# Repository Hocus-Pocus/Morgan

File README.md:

# Morgan
2001 Dodge Ram 2500, 4x4, Extended cab, Long box. Originally equiped with the 360CID V8 engine, automatic transmision and Dana 60 HD rear axle. Drive train changed to 1995 Dodge 488CID (8.0L) V 10 engine, NV4500 5 speed manual transmission, Dana 80 limited slip rear axle, custom built programmable EFI.

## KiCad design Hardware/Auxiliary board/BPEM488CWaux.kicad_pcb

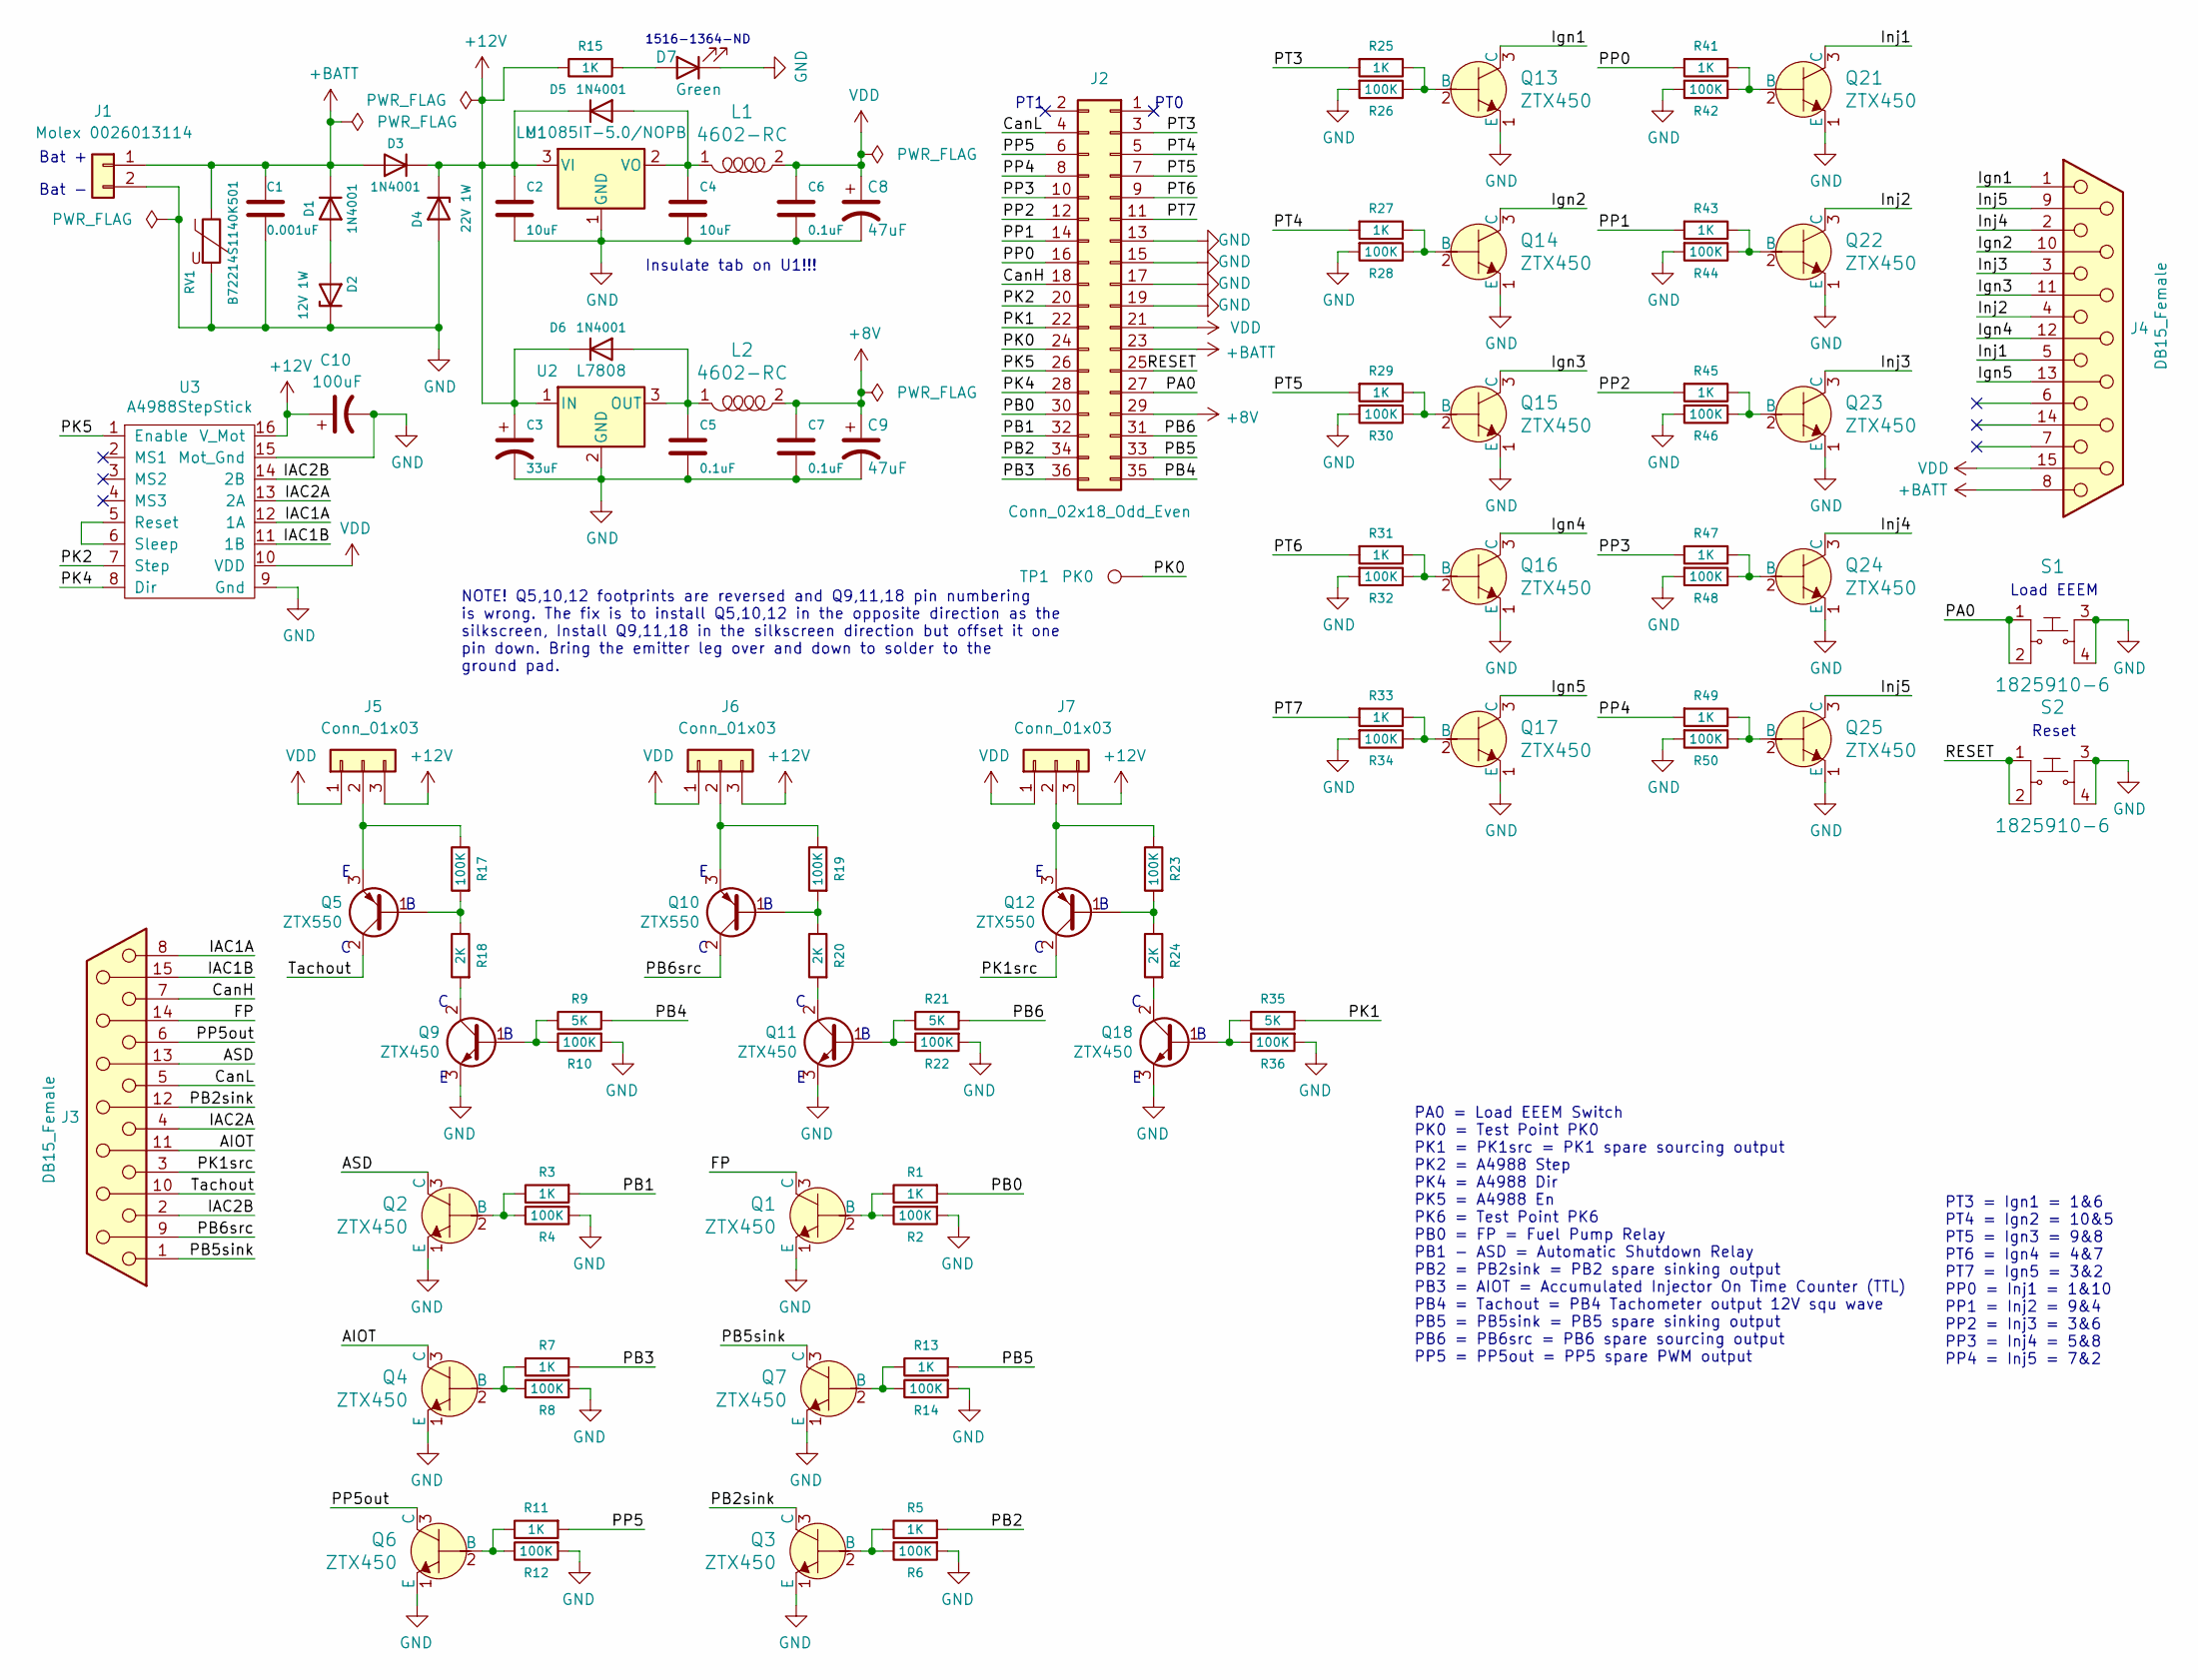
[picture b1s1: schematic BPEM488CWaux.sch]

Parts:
C1: 0.001uF; C_Disc_D3.8mm_W2.6mm_P2.50mm; Digikey 399-13913-2-ND
C2, C4: 10uF; C_Disc_D5.0mm_W2.5mm_P2.50mm; Digikey 399-13950-ND
C3: 33uF; CP_Radial_Tantal_D8.0mm_P5.00mm; Digikey 399-3591-ND
C5, C6, C7: 0.1uF; C_Disc_D5.0mm_W2.5mm_P2.50mm; Digikey 399-4264-ND
C8, C9: 47uF; CP_Radial_Tantal_D8.0mm_P5.00mm; Digikey 399-3596-ND
C10: 100uF; CP_Radial_Tantal_D8.0mm_P5.00mm; Digikey 399-3596-ND
D1, D3, D5, D6: 1N4001; D_DO-41_SOD81_P7.62mm_Horizontal; Digikey 1N4001DICT-ND
D2: 12V 1W; D_DO-41_SOD81_P7.62mm_Horizontal; Digikey 1727-3635-2-ND
D4: 22V 1W; D_DO-41_SOD81_P7.62mm_Horizontal; Digikey MAZ222000GTR-ND
D7: Green; LED_D5.0mm; Digikey 1516-1364-ND
J1: Molex 0026013114; Molex_Mini-Fit_Jr_5569-02A2_2x01_P4.20mm_Horizontal; Digikey WM14505-ND
J2: Conn_02x18_Odd_Even; PinSocket_2x18_P2.54mm_Vertical
J3, J4: DB15_Female; DSUB-15_Female_Horizontal_P2.77x2.84mm_EdgePinOffset7.70mm_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; Digikey A32123-ND
J5, J6, J7: Conn_01x03; PinHeader_1x03_P2.54mm_Vertical
L1, L2: 4602-RC; L_Axial_L16.0mm_D6.3mm_P25.40mm_Horizontal_Fastron_VHBCC; Digikey 4602-RC-ND
Q1, Q2, Q3, Q4, Q6, Q7, Q13, Q14, Q15, Q16, Q17, Q21, Q22, Q23, Q24, Q25: ZTX450; MPN ZTX450; Digi-Key_PN ZTX450-ND
Q5, Q10, Q12: ZTX550
Q9, Q11, Q18: ZTX450
R1, R3, R5, R7, R11, R13, R15, R25, R27, R29, R31, R33, R41, R43, R45, R47, R49: 1K; R_Axial_DIN0207_L6.3mm_D2.5mm_P10.16mm_Horizontal; Digikey 1.00KXBK-ND
R2, R4, R6, R8, R10, R12, R14, R22, R26, R28, R30, R32, R34, R36, R42, R44, R46, R48, R50: 100K; R_Axial_DIN0207_L6.3mm_D2.5mm_P10.16mm_Horizontal; Digikey 100KXBK-ND
R9, R21, R35: 5K; R_Axial_DIN0207_L6.3mm_D2.5mm_P10.16mm_Horizontal; Digikey 1.00KXBK-ND
R17, R19, R23: 100K; R_Axial_DIN0207_L6.3mm_D2.5mm_P10.16mm_Horizontal; Digikey 1.00KXBK-ND
R18, R20, R24: 2K; R_Axial_DIN0207_L6.3mm_D2.5mm_P10.16mm_Horizontal; Digikey 1.00KXBK-ND
RV1: B72214S1140K501; RV_Disc_D15.5mm_W3.9mm_P7.5mm; Digikey 495-2057-ND
S1, S2: 1825910-6; Switch_Tactile_THT_6x6mm; MPN 1825910-6; Digi-Key_PN 450-1650-ND
TP1: PK0; PinHeader_1x01_P2.54mm_Vertical
U1: LM1085IT-5.0/NOPB; LM1085
U2: L7808
U3: A4988StepStick

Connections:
+8V: C7.1, C9.1, J2.29, L2.2
+12V: C2.1, C3.1, C10.1, D3.1 (K), D4.1 (K), D5.1 (K), D6.1 (K), J5.3, J6.3, J7.3, R15.1, U1.3 (VI), U2.1 (IN), U3.16 (V_Mot)
+BATT: C1.1, D1.1 (K), D3.2 (A), J1.1, J2.23, J4.8, RV1.1
/AIOT: J3.11 (P111), Q4.3 (C)
/ASD: J3.13, Q2.3 (C)
/CanH: J2.18, J3.7
/CanL: J2.4, J3.5
/FP: J3.14, Q1.3 (C)
/IAC1A: J3.8, U3.12 (1A)
/IAC1B: J3.15, U3.11 (1B)
/IAC2A: J3.4, U3.13 (2A)
/IAC2B: J3.2, U3.14 (2B)
/Ign1: J4.1, Q13.3 (C)
/Ign2: J4.10, Q14.3 (C)
/Ign3: J4.11 (P111), Q15.3 (C)
/Ign4: J4.12, Q16.3 (C)
/Ign5: J4.13, Q17.3 (C)
/Inj1: J4.5, Q21.3 (C)
/Inj2: J4.4, Q22.3 (C)
/Inj3: J4.3, Q23.3 (C)
/Inj4: J4.2, Q24.3 (C)
/Inj5: J4.9, Q25.3 (C)
/PA0: J2.27, S1.1, S1.2
/PB0: J2.30, R1.2
/PB1: J2.32, R3.2
/PB2: J2.34, R5.2
/PB2sink: J3.12, Q3.3 (C)
/PB3: J2.36, R7.2
/PB4: J2.35, R9.2
/PB5: J2.33, R13.2
/PB5sink: J3.1, Q7.3 (C)
/PB6: J2.31, R21.2
/PB6src: J3.9, Q10.2 (C)
/PK0: J2.24, TP1.1
/PK1: J2.22, R35.2
/PK1src: J3.3, Q12.2 (C)
/PK2: J2.20, U3.7 (Step)
/PK4: J2.28, U3.8 (Dir)
/PK5: J2.26, U3.1 (Enable)
/PP0: J2.16, R41.2
/PP1: J2.14, R43.2
/PP2: J2.12, R45.2
/PP3: J2.10, R47.2
/PP4: J2.8, R49.2
/PP5: J2.6, R11.2
/PP5out: J3.6, Q6.3 (C)
/PT3: J2.3, R25.2
/PT4: J2.5, R27.2
/PT5: J2.7, R29.2
/PT6: J2.9, R31.2
/PT7: J2.11, R33.2
/RESET: J2.25, S2.1, S2.2
/Tachout: J3.10, Q5.2 (C)
GND: C1.2, C2.2, C3.2, C4.2, C5.2, C6.2, C7.2, C8.2, C9.2, C10.2, D2.1 (K), D4.2 (A), D7.1 (K), J1.2, J2.13, J2.15, J2.17, J2.19, Q1.1 (E), Q2.1 (E), Q3.1 (E), Q4.1 (E), Q6.1 (E), Q7.1 (E), Q9.3 (E), Q11.3 (E), Q13.1 (E), Q14.1 (E), Q15.1 (E), Q16.1 (E), Q17.1 (E), Q18.3 (E), Q21.1 (E), Q22.1 (E), Q23.1 (E), Q24.1 (E), Q25.1 (E), R2.2, R4.2, R6.2, R8.2, R10.2, R12.2, R14.2, R22.2, R26.2, R28.2, R30.2, R32.2, R34.2, R36.2, R42.2, R44.2, R46.2, R48.2, R50.2, RV1.2, S1.3, S1.4, S2.3, S2.4, U1.1 (GND), U2.2 (GND), U3.9 (Gnd), U3.15 (Mot_Gnd)
unnamed: C4.1, D5.2 (A), L1.1, U1.2 (VO)
unnamed: C5.1, D6.2 (A), L2.1, U2.3 (OUT)
unnamed: D1.2 (A), D2.2 (A)
unnamed: D7.2 (A), R15.2
unnamed: J5.2, Q5.3 (E), R17.1
unnamed: J6.2, Q10.3 (E), R19.1
unnamed: J7.2, Q12.3 (E), R23.1
unnamed: Q1.2 (B), R1.1, R2.1
unnamed: Q2.2 (B), R3.1, R4.1
unnamed: Q3.2 (B), R5.1, R6.1
unnamed: Q4.2 (B), R7.1, R8.1
unnamed: Q5.1 (B), R17.2, R18.1
unnamed: Q6.2 (B), R11.1, R12.1
unnamed: Q7.2 (B), R13.1, R14.1
unnamed: Q9.1 (B), R9.1, R10.1
unnamed: Q9.2 (C), R18.2
unnamed: Q10.1 (B), R19.2, R20.1
unnamed: Q11.1 (B), R21.1, R22.1
unnamed: Q11.2 (C), R20.2
unnamed: Q12.1 (B), R23.2, R24.1
unnamed: Q13.2 (B), R25.1, R26.1
unnamed: Q14.2 (B), R27.1, R28.1
unnamed: Q15.2 (B), R29.1, R30.1
unnamed: Q16.2 (B), R31.1, R32.1
unnamed: Q17.2 (B), R33.1, R34.1
unnamed: Q18.1 (B), R35.1, R36.1
unnamed: Q18.2 (C), R24.2
unnamed: Q21.2 (B), R41.1, R42.1
unnamed: Q22.2 (B), R43.1, R44.1
unnamed: Q23.2 (B), R45.1, R46.1
unnamed: Q24.2 (B), R47.1, R48.1
unnamed: Q25.2 (B), R49.1, R50.1
unnamed: U3.5 (Reset), U3.6 (Sleep)
VDD: C6.1, C8.1, J2.21, J4.15, J5.1, J6.1, J7.1, L1.2, U3.10 (VDD)

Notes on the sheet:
Load EEEM
Reset
Bat -
Bat +
PA0 = Load EEEM Switch PK0 = Test Point PK0 PK1 = PK1src = PK1 spare sourcing output PK2 = A4988 Step PK4 = A4988 Dir PK5 = A4988 En PK6 = Test Point PK6 PB0 = FP = Fuel Pump Relay PB1 - ASD = Automatic Shutdown Relay PB2 = PB2sink = PB2 spare sinking output PB3 = AIOT = Accumulated Injector On Tim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
PT3 = Ign1 = 1&6 PT4 = Ign2 = 10&5 PT5 = Ign3 = 9&8 PT6 = Ign4 = 4&7 PT7 = Ign5 = 3&2 PP0 = Inj1 = 1&10 PP1 = Inj2 = 9&4 PP2 = Inj3 = 3&6 PP3 = Inj4 = 5&8 PP4 = Inj5 = 7&2
Insulate tab on U1!!!
PT0
PT1
1516-1364-ND
NOTE! Q5,10,12 footprints are reversed and Q9,11,18 pin numbering is wrong. The fix is to install Q5,10,12 in the opposite direction as the silkscreen, Install Q9,11,18 in the silkscreen direction but offset it one pin down. Bring the emitter leg over and down to solder to the ground pad.

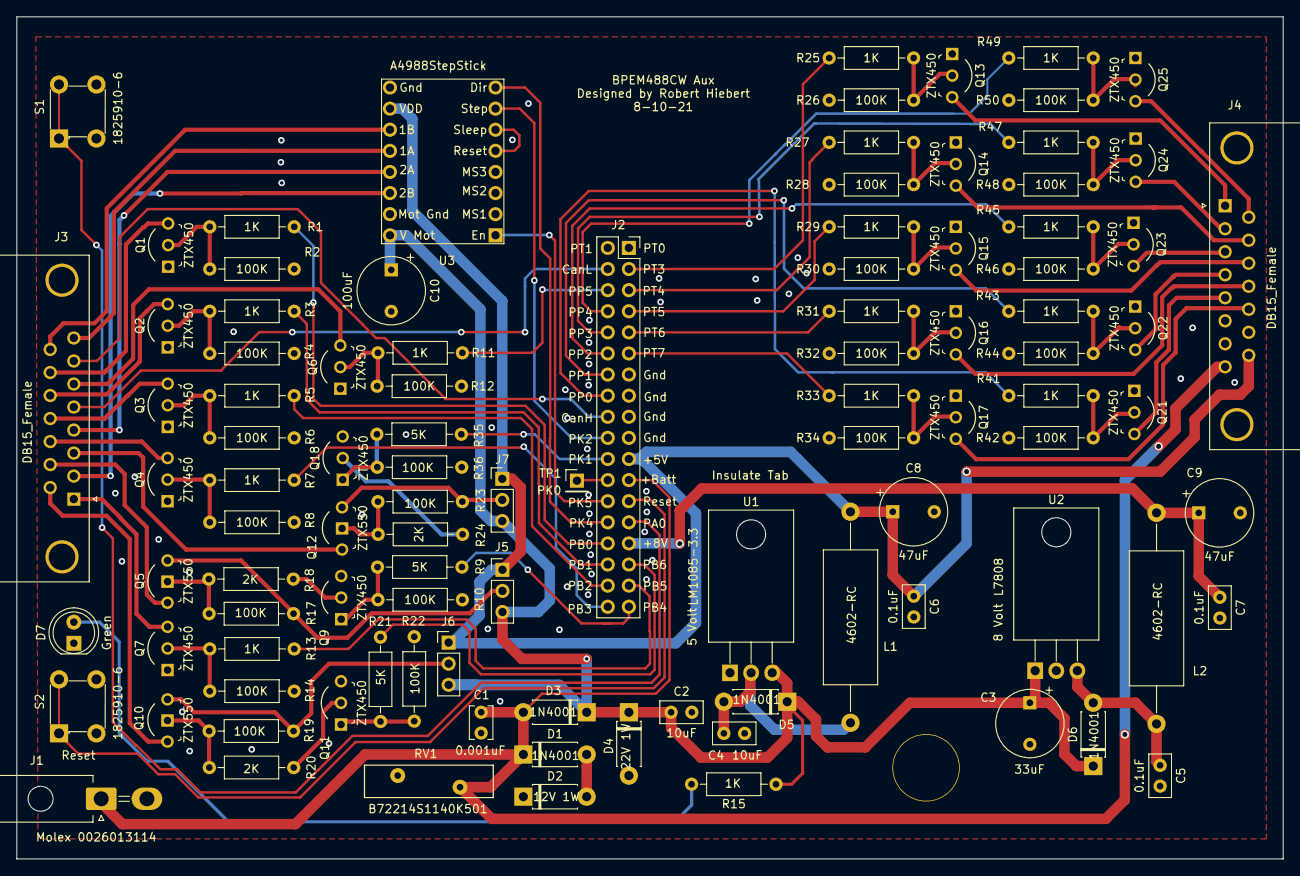
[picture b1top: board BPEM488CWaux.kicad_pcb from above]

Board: 2 copper layers, 152.4 x 101.3 mm, 100 parts (0 on the bottom side), 88 nets.

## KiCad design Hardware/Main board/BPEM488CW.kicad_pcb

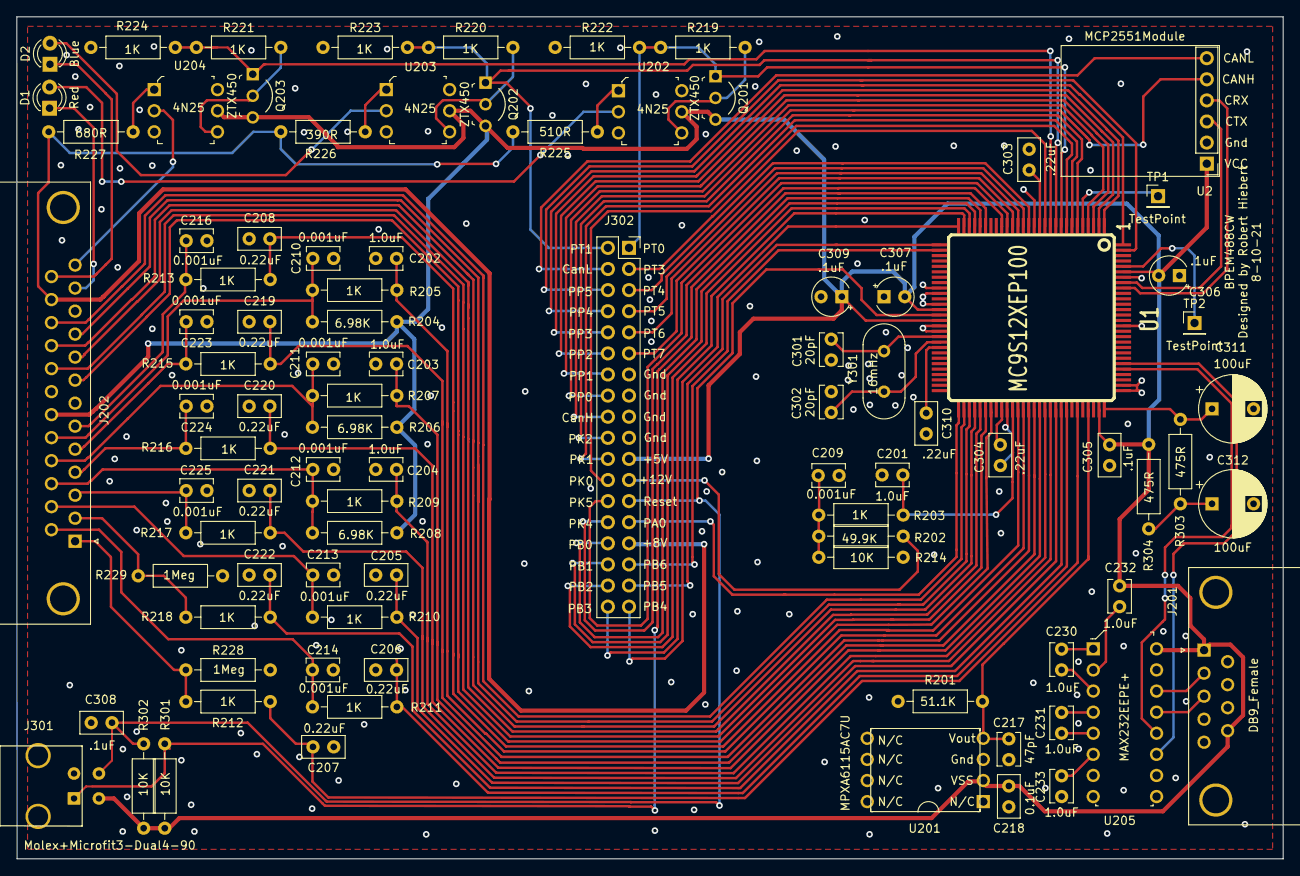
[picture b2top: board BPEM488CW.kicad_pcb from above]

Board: 2 copper layers, 152.4 x 101.3 mm, 92 parts (0 on the bottom side), 98 nets.

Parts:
C201, C202, C203, C204, C230, C231, C232, C233: 1.0uF; C_Disc_D3.8mm_W2.6mm_P2.50mm
C205, C206, C207, C208, C219, C220, C221, C222: 0.22uF; C_Disc_D5.0mm_W2.5mm_P2.50mm
C209, C210, C211, C212, C213, C214, C216, C223, C224, C225: 0.001uF; C_Disc_D3.8mm_W2.6mm_P2.50mm
C217: 47pF; C_Disc_D3.8mm_W2.6mm_P2.50mm
C218: 0.1uF; C_Disc_D5.0mm_W2.5mm_P2.50mm
C301, C302: 20pF; C_Disc_D3.8mm_W2.6mm_P2.50mm
C303, C304, C310: .22uF; C_Disc_D5.0mm_W2.5mm_P2.50mm
C305, C308: .1uF; C_Disc_D5.0mm_W2.5mm_P2.50mm
C306, C307, C309: .1uF; CP_Radial_Tantal_D4.5mm_P2.50mm
C311, C312: 100uF; CP_Radial_D8.0mm_P5.00mm
D1: Red; LED_D3.0mm
D2: Blue; LED_D3.0mm
J201: DB9_Female; DSUB-9_Female_Horizontal_P2.77x2.84mm_EdgePinOffset9.90mm_H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
J202: DB25_Female; DSUB-25_Female_Horizontal_P2.77x2.84mm_EdgePinOffset7.70mm_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
J301: Molex+Microfit3-Dual4-90; Molex-Microfit3-Dual4-90
J302: Conn_02x18_Odd_Even; PinSocket_2x18_P2.54mm_Vertical
Q201, Q202, Q203: ZTX450; TO-92-3_Formed_Leads
R201: 51.1K; R_Axial_DIN0207_L6.3mm_D2.5mm_P10.16mm_Horizontal
R202: 49.9K; R_Axial_DIN0207_L6.3mm_D2.5mm_P10.16mm_Horizontal
R203, R205, R207, R209, R210, R211, R212, R213, R215, R216, R217, R218, R219, R220, R221, R222, R223, R224: 1K; R_Axial_DIN0207_L6.3mm_D2.5mm_P10.16mm_Horizontal
R204, R206, R208: 6.98K; R_Axial_DIN0207_L6.3mm_D2.5mm_P10.16mm_Horizontal
R214, R301, R302: 10K; R_Axial_DIN0207_L6.3mm_D2.5mm_P10.16mm_Horizontal
R225: 510R; R_Axial_DIN0207_L6.3mm_D2.5mm_P10.16mm_Horizontal
R226: 390R; R_Axial_DIN0207_L6.3mm_D2.5mm_P10.16mm_Horizontal
R227: 680R; R_Axial_DIN0207_L6.3mm_D2.5mm_P10.16mm_Horizontal
R228, R229: 1Meg; R_Axial_DIN0207_L6.3mm_D2.5mm_P10.16mm_Horizontal
R303, R304: 475R; R_Axial_DIN0207_L6.3mm_D2.5mm_P10.16mm_Horizontal
TP1, TP2: TestPoint; PinHeader_1x01_P2.54mm_Vertical
U1: MC9S12XEP100
U2: MCP2551Module
U201: MPXA6115AC7U
U202, U203, U204: 4N25; DIP-6_W7.62mm
U205: MAX232EEPE+; DIP-16_W7.62mm
Y301: 16mHz; Crystal_HC49-4H_Vertical

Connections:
+8V: J202.24, J302.29, R225.1, R226.1, R227.1
+BATT: J302.23, R202.2
/CPU/CanH: J302.18, U2.5
/CPU/CanL: J302.4, U2.6
/CPU/PA0: J302.27, U1.57
/CPU/PB0: J302.30, U1.24
/CPU/PB1: J302.32, U1.25
/CPU/PB2: J302.34, U1.26
/CPU/PB3: J302.36, U1.27
/CPU/PB4: J302.35, U1.28
/CPU/PB5: J302.33, U1.29
/CPU/PB6: J302.31, U1.30
/CPU/PK0: J302.24, U1.8
/CPU/PK1: J302.22, U1.7
/CPU/PK2: J302.20, U1.6
/CPU/PK3: TP1.1, U1.5
/CPU/PK4: J302.28, U1.20
/CPU/PK5: J302.26, U1.19
/CPU/PK7: TP2.1, U1.108
/CPU/PP0: J302.16, U1.4
/CPU/PP1: J302.14, U1.3
/CPU/PP2: J302.12, U1.2
/CPU/PP3: J302.10, U1.1
/CPU/PP4: J302.8, U1.112
/CPU/PP5: J302.6, U1.111
/CPU/PT3: J302.3, U1.12
/CPU/PT4: J302.5, U1.15
/CPU/PT5: J302.7, U1.16
/CPU/PT6: J302.9, U1.17
/CPU/PT7: J302.11, U1.18
/CPU/RESET: C308.1, J301.4, J302.25, R302.2, U1.42
/Inputs_RS232/CKP: D2.1, J202.25
/Inputs_RS232/CLT: C210.2, J202.18, R204.1, R205.1
/Inputs_RS232/CMP: D1.1, J202.12
/Inputs_RS232/EFP: C223.2, J202.5, R215.1
/Inputs_RS232/EGO1: J202.1, R212.1, R228.1
/Inputs_RS232/EGO2: J202.2, R218.1, R229.1
/Inputs_RS232/EOP: C216.2, J202.6, R213.1
/Inputs_RS232/Ftrm: C225.2, J202.3, R217.1
/Inputs_RS232/Itrm: C224.2, J202.4, R216.1
/Inputs_RS232/MAP: C213.2, J202.15, R210.1
/Inputs_RS232/MAT: C211.2, J202.17, R206.1, R207.1
/Inputs_RS232/PAD03in: C212.2, J202.16, R208.1, R209.1
/Inputs_RS232/TPS: C214.2, J202.14, R211.1
/Inputs_RS232/VSPD: J202.13, U204.2
GND: C201.1, C202.1, C203.1, C204.1, C205.1, C206.1, C207.1, C208.1, C209.1, C210.1, C211.1, C212.1, C213.1, C214.1, C216.1, C217.1, C218.2, C219.1, C220.1, C221.1, C222.1, C223.1, C224.1, C225.1, C233.1, C301.1, C302.1, C303.1, C304.1, C305.1, C306.1, C307.1, C308.2, C309.2, C310.2, C311.2, C312.2, J201.5, J202.7, J202.11, J202.20, J301.2, J302.13, J302.15, J302.17, J302.19, R201.2, R214.1, R222.1, R223.1, R224.1, R228.2, R229.2, U1.14, U1.37, U1.38, U1.40, U1.44, U1.45, U1.66, U1.85, U1.86, U1.97, U1.106, U2.2, U201.3, U205.15
unnamed: C209.2, R202.1, R203.1, R214.2
unnamed: C230.1, U205.3
unnamed: C230.2, U205.1
unnamed: C231.1, U205.5
unnamed: C231.2, U205.4
unnamed: C232.1, U205.2
unnamed: C233.2, U205.6
unnamed: C301.2, U1.46, Y301.2
unnamed: C302.2, U1.47, Y301.1
unnamed: C303.2, U1.13
unnamed: C304.2, U1.65
unnamed: C310.1, U1.48
unnamed: C311.1, R303.1, U1.84
unnamed: C312.1, R303.2, R304.1
unnamed: D1.2, U202.2
unnamed: D2.2, U203.2
unnamed: J201.2, U205.14
unnamed: J201.3, U205.13
unnamed: J301.1, R301.2, U1.23
unnamed: Q201.2, R219.2, U202.4
unnamed: Q202.2, R220.2, U203.4
unnamed: Q203.2, R221.2, U204.4
unnamed: R225.2, U202.1
unnamed: R226.2, U203.1
unnamed: R227.2, U204.1
PA1: J202.23, U1.58
PA2: J202.10, U1.59
PA3: J202.22, U1.60
PA4: J202.9, U1.61
PA5: J202.21, U1.62
PA6: J202.8, U1.63
PAD00: C201.2, R203.2, U1.67
PAD01: C202.2, R205.2, U1.69
PAD02: C203.2, R207.2, U1.71
PAD03: C204.2, R209.2, U1.73
PAD04: C205.2, R210.2, U1.75
PAD05: C206.2, R211.2, U1.77
PAD06: C207.2, R212.2, U1.79
PAD07: C217.2, R201.1, U1.81, U201.4
PAD08: C208.2, R213.2, U1.68
PAD09: C219.2, R215.2, U1.70
PAD10: C220.2, R216.2, U1.72
PAD11: C221.2, R217.2, U1.74
PAD12: C222.2, R218.2, U1.76
PM0: U1.105, U2.3
PM1: U1.104, U2.4
PS0: U1.89, U205.12
PS1: U1.90, U205.11
PT0: J302.1, Q201.1, R219.1, R222.2, U1.9
PT1: J302.2, Q202.1, R220.1, R223.2, U1.10
PT2: Q203.1, R221.1, R224.2, U1.11
VDD: C218.1, C232.2, C305.2, C306.2, C307.2, C309.1, J201.1, J201.9, J202.19, J301.3, J302.21, Q201.3, Q202.3, Q203.3, R204.2, R206.2, R208.2, R301.1, R302.1, R304.2, U1.41, U1.43, U1.83, U1.107, U2.1, U201.2, U202.5, U203.5, U204.5, U205.16

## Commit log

2022-11-16 Create Git Hold
